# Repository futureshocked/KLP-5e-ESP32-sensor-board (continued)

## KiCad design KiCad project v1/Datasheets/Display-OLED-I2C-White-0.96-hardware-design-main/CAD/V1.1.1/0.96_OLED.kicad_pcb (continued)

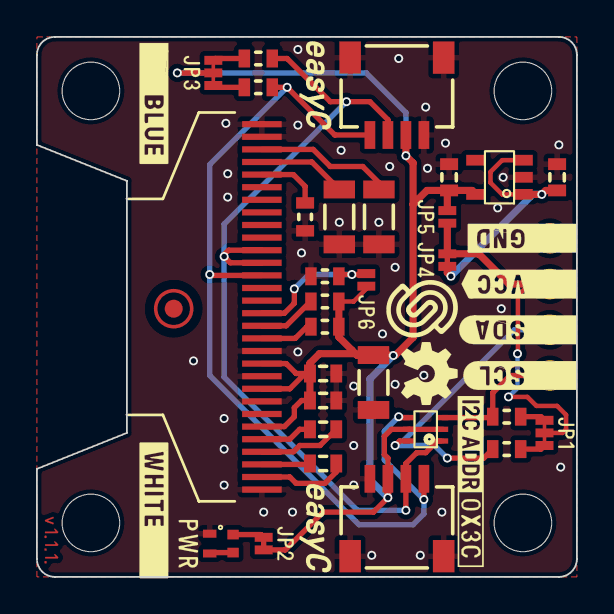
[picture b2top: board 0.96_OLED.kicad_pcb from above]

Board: 2 copper layers, 30.0 x 30.0 mm, 36 parts (0 on the bottom side), 24 nets.

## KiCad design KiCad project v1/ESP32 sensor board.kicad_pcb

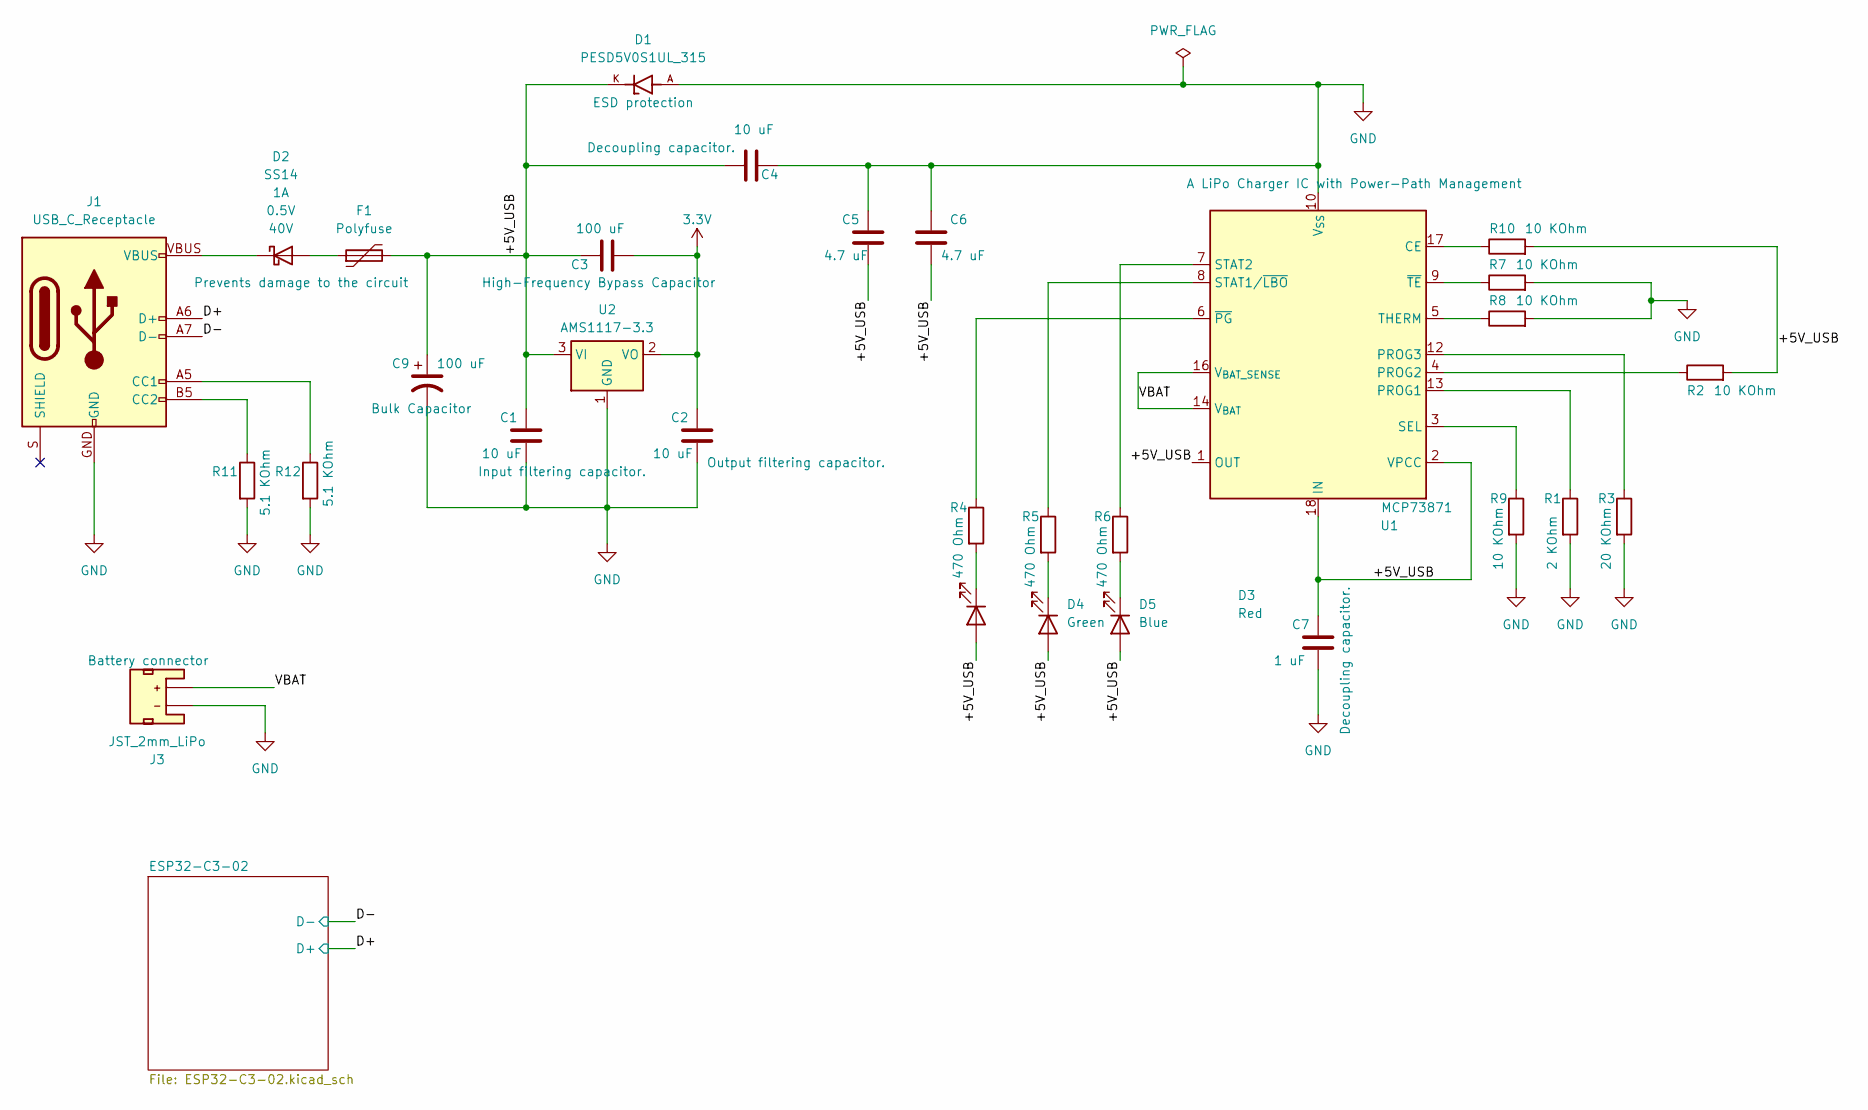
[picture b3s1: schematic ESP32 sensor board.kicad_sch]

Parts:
C1, C2, C4: 10 uF; C_0805_2012Metric; Voltage 1kV; Tolerance 100%
C3, C9: 100 uF; C_0805_2012Metric; Voltage 1kV; Tolerance 100%
C5, C6: 4.7 uF; C_0805_2012Metric; Voltage 1kV; Tolerance 100%
C7: 1 uF; C_0805_2012Metric; Voltage 1kV; Tolerance 100%
D1: PESD5V0S1UL_315; DIO_PESD5V0S1UL_315; PARTREV 15 January 2020
D2: SS14; SMA
D3: Red; LED_0603_1608Metric
D4: Green; LED_0603_1608Metric
D5: Blue; LED_0603_1608Metric
F1: Polyfuse; 1210
J1: USB_C_Receptacle; USB-C_16
J3: JST_2mm_LiPo; JST_SMD_2.0mm-2
R1: 2 KOhm; R_0805_2012Metric
R2, R7, R8, R9, R10: 10 KOhm; R_0805_2012Metric
R3: 20 KOhm; R_0805_2012Metric
R4, R5, R6: 470 Ohm; R_0805_2012Metric
R11, R12: 5.1 KOhm; R_0805_2012Metric
U1: MCP73871; QFN-20-1EP_4x4mm_P0.5mm_EP2.5x2.5mm
U2: AMS1117-3.3; SOT-223-3_TabPin2

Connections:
3.3V: C2.1, C3.2, U2.2 (VO); also elsewhere on the board
/+5V_USB: C1.1, C3.1, C4.2, C5.2, C6.2, C7.1, C9.1, D1.K, D3.2 (A), D4.2 (A), D5.2 (A), F1.2, R2.2, R10.2, U1.1 (OUT), U1.2 (VPCC), U1.18 (IN), U1.19 (IN), U1.20 (OUT), U2.3 (VI)
/D+: J1.A6 (D+), J1.B6 (D+); also elsewhere on the board
/D-: J1.A7 (D-), J1.B7 (D-); also elsewhere on the board
/VBAT: J3.2 (+), U1.14 (V_{BAT}), U1.15 (V_{BAT}), U1.16 (V_{BAT_SENSE})
GND: C1.2, C2.2, C4.1, C5.1, C6.1, C7.2, C9.2, D1.A, J1.GND, J3.1 (-), R1.2, R3.2, R7.2, R8.2, R9.2, R11.2, R12.2, U1.10 (V_{SS}), U1.11 (V_{SS}), U1.21 (V_{SS}), U2.1 (GND); also elsewhere on the board
unnamed: D2.A, F1.1
unnamed: D2.C, J1.VBUS
unnamed: D3.1 (K), R4.2
unnamed: D4.1 (K), R5.2
unnamed: D5.1 (K), R6.2
unnamed: J1.A5 (CC1), R12.1
unnamed: J1.B5 (CC2), R11.1
unnamed: R10.1, U1.17 (CE)
unnamed: R1.1, U1.13 (PROG1)
unnamed: R2.1, U1.4 (PROG2)
unnamed: R3.1, U1.12 (PROG3)
unnamed: R9.1, U1.3 (SEL)
unnamed: R5.1, U1.8 (STAT1/~LBO)
unnamed: R6.1, U1.7 (STAT2)
unnamed: R8.1, U1.5 (THERM)
unnamed: R4.1, U1.6 (~PG)
unnamed: R7.1, U1.9 (~TE)

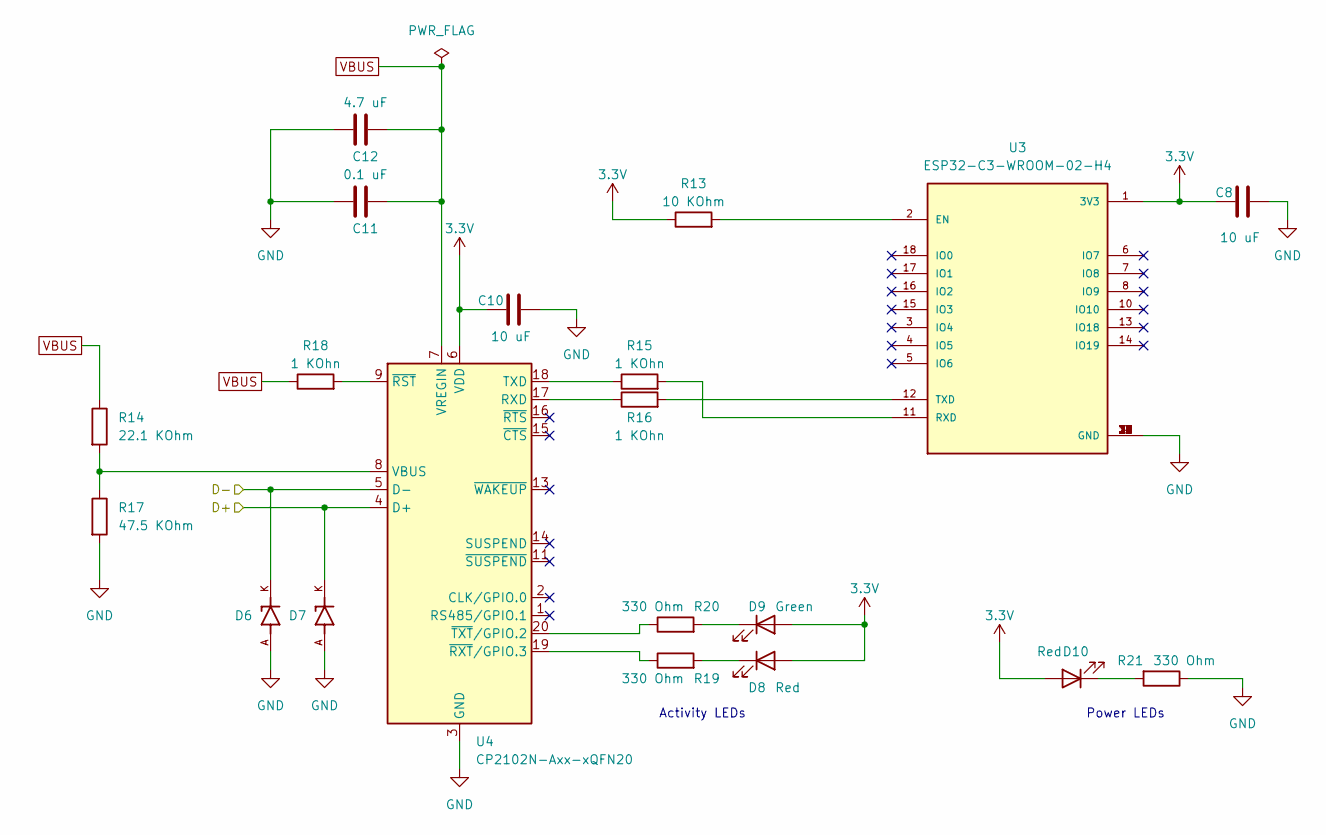
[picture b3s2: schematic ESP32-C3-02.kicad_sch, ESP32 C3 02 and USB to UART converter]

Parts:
C8, C10: 10 uF; C_0805_2012Metric; Voltage 1kV; Tolerance 100%
C11: 0.1 uF; C_0805_2012Metric; Voltage 1kV; Tolerance 100%
C12: 4.7 uF; C_0805_2012Metric; Voltage 1kV; Tolerance 100%
D6, D7: PESD5V0S1UL_315; DIO_PESD5V0S1UL_315; PARTREV 15 January 2020
D8, D10: Red; LED_0603_1608Metric
D9: Green; LED_0603_1608Metric
R13: 10 KOhm; R_0805_2012Metric
R14: 22.1 KOhm; R_0805_2012Metric
R15, R16, R18: 1 KOhn; R_0805_2012Metric
R17: 47.5 KOhm; R_0805_2012Metric
R19, R20, R21: 330 Ohm; R_0805_2012Metric
U3: ESP32-C3-WROOM-02-H4; MODULE_ESP32-C3-WROOM-02-H4
U4: CP2102N-Axx-xQFN20; SiliconLabs_QFN-20-1EP_3x3mm_P0.5mm_EP1.8x1.8mm

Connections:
3.3V: C8.1, C10.1, D8.2 (A), D9.2 (A), D10.2 (A), R13.1, U3.1 (3V3), U4.6 (VDD); also elsewhere on the board
/D+: D7.K, U4.4 (D+); also elsewhere on the board
/D-: D6.K, U4.5 (D-); also elsewhere on the board
GND: C8.2, C10.2, C11.2, C12.2, D6.A, D7.A, R17.2, R21.1, U3.9 (GND), U3.19 (GND), U3.20 (GND), U3.21 (GND), U3.22 (GND), U3.23 (GND), U3.24 (GND), U3.25 (GND), U3.26 (GND), U3.27 (GND), U3.28 (GND), U3.29 (GND), U3.30 (GND), U3.31 (GND), U3.32 (GND), U3.33 (GND), U3.34 (GND), U3.35 (GND), U3.36 (GND), U3.37 (GND), U3.38 (GND), U3.39 (GND), U4.3 (GND), U4.12 (GND), U4.21 (GND); also elsewhere on the board
unnamed: D8.1 (K), R19.2
unnamed: D9.1 (K), R20.2
unnamed: D10.1 (K), R21.2
unnamed: R13.2, U3.2 (EN)
unnamed: R15.2, U3.11 (RXD)
unnamed: R16.2, U3.12 (TXD)
unnamed: R16.1, U4.17 (RXD)
unnamed: R15.1, U4.18 (TXD)
unnamed: R14.2, R17.1, U4.8 (VBUS)
unnamed: R18.2, U4.9 (~RST)
unnamed: R19.1, U4.19 (~RXT/GPIO.3)
unnamed: R20.1, U4.20 (~TXT/GPIO.2)
VBUS: C11.1, C12.1, R14.1, R18.1, U4.7 (VREGIN)

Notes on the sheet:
Activity LEDs
Power LEDs

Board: 2 copper layers, 50 parts (0 on the bottom side), 36 nets, no tracks yet.

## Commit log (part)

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2024-11-22 Backlink to CADLAB.io has been added.
2024-11-22 Starting integration of the ESP32.
2024-11-23 Completed first revision of the ESP32 and CP2102 integration.
2024-11-23 Created the draft layout, and inserted available footprints.
2024-11-28 Exluding the backups repository.
2024-11-28 Excluding various KiCad files from the repository.
2024-11-29 Added flash memory module and microsd module to the designed. Moved the libraries and datasheets in the project folder.
2024-11-29 Added sensors to the schematic design.
2024-11-30 Added an OLED I2C display connector, boot and reset buttons, and breakout for remaining pins.
2024-11-30 Remove deleted files
2024-12-03 Created netclasses and assigned nets.
2024-12-03 Completed symbol and footprint associations.
2024-12-05 Small fixes.
2024-12-06 Simplifying component values by removing units.
2024-12-11 Changed the name of the project folder, no need for version number.
2024-12-11 Fixed lots of bugs.
2024-12-12 Configured the layout editor.
2024-12-12 Completed draft layout.
2024-12-12 Experimenting with lenght tuning of the USB data tracks.
2024-12-12 Autorouting experiment. Layout is incomplete.
2024-12-12 Trying routing, layout, and changed USB and battery connectors.
2024-12-12 Replaced the button, USB, bat connector with new symbols and footprints. Completed draft layout and routing.
2024-12-13 Removed redundant layout backup file.
2024-12-13 Added draft BOM.
2024-12-13 Replaced tantalum capacitors and LEDs.
2024-12-14 Layout in progress.
2024-12-14 Added 3D models.
2024-12-14 Completed layout and 3D models, next up is review everything.
2024-12-16 Completed draft of the layout.
2024-12-20 Replaced USB C receptacle with a different model. Repositioning components to better align with manufacturer recommendations.
2024-12-20 Work in progress, new layout and routing.
2024-12-20 Moving thigns around.
2024-12-21 Completed layout for v2.
2024-12-23 Introduced new parts that can be purchased for manufacturing by NextPCB. Corrected numerous issues.
2024-12-23 Updated U1 footprint to better match the component we can order from Microchip.
2024-12-26 Optimisation complete.
2024-12-26 Removed old files.
2024-12-27 Additional checks completed, and Gerbers exported for HQDFM. Looking good for manufacturing.
2025-01-23 Update LICENSE
    Now using the CERN-OHL-S (Strongly Reciprocal). This variant requires that any modifications or derivatives of the licensed material be distributed under the same license terms, ensuring that all der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
2025-02-28 Fixed and improved Schematic design:
    * Changed the buttons
    * Added a ferrite bead at the output of the charger to cut some possible noise.
    * Changed the values of R30, R31 and C19, and i add a 100K trimmer to set the gain from 25x to 125x.
    * Added C23, C24 and C25 in the photo sensor circuit
2025-02-28 Added updated BOM file.
2025-03-03 Completed symbol-footprint associations.
2025-03-03 Completed schematic fixes and updates. Continuing with the layout for Prototype #2.
2025-03-03 Added updated BOM.
2025-03-03 Finished layout update for prototype #2.
2025-03-03 Added a diagram that shows the changes in prototype #2 in a graphical way.
2025-03-03 Swapped pins for CS_SD and MIC_OUT so that the microphone is connected to a usable ADC.
2025-03-03 Minor text adjustements.
2025-05-12 Added missing data in BOM
2025-09-10 Set correct SW1 and SW2 symbols
2026-06-29 Submitted BOM for assembly
